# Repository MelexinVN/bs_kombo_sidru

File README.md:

# СИДРУ
## СветоИзлучающее Декоративное Радиоуправляемое Устройство

В рамках проекта ["КомБО"](https://github.com/MelexinVN/bs_kombo) разработано декоративное устройство на адресных светодиодах, управляемое по радиоканалу.

Устройство состоит из двух частей - декоративная часть и пульт управления.

Обе части содержат схему управления на микроконтроллере stm32f030f4p6, радиомодуль nrf24l01+, и схему питания.
В декоративной части микроконтроллер управляет адресными светодиодами ws2812. 
В данном случае светодиоды расположены на модуле в виде кольца (могут быть отдельными модулями, в виде светодиодной ленты и т.п.)

В пульте управления микроконтроллер в зависимости от состояния чувствительного элемента отправляет различные команды в ответ на запросы декоративного устройства.

Здесь в качестве чувствительных элементов используются датчики касания TTP223 (могут быть использованы кнопки, выходы реле, герконы и т.п.)

As part of the "КомБО" project, a decorative device based on addressable LEDs, controlled via a radio channel, has been developed.

The device consists of two parts - a decorative part and a control panel.

Both parts contain a control circuit on the stm32f030f4p6 microcontroller, an nrf24l01+ radio module, and a power supply circuit.
In the decorative part, the microcontroller controls the ws2812 addressable LEDs.
In this case, the LEDs are located on the module in the form of a ring (can be separate modules, in the form of an LED strip, etc.)

In the control panel, the microcontroller, depending on the state of the sensitive element, sends various commands in response to requests from the decorative device.

Here, TTP223 touch sensors are used as sensitive elements (buttons, relays, etc. can be used)

## Схема соединений пульта управления. Control panel connection diagram

## Схема соединений декоративной части. Connection diagram of the decorative part

## Пример готового устройства. Example of a finished device

### Планы по развитию:
- **Добавление новых световых эффектов**
- **Добавление исполнений для других микроконтроллеров и большего числа светодиодов**
- **Проекты исходников на других IDE, в частности STM32CubeIDE**
- **Пример исполнения для подсветки комнаты**

### Development plans:
- **Adding new lighting effects**
- **Add versions for other microcontrollers and more LEDs**
- **Source projects on other IDEs, in particular STM32CubeIDE**
- **Example of design for room lighting**

### Репозиторий содержит:
- ***Исполняемые файлы и исходники ПО декоративной части и пульта управления***. Программы разработаны в Keil µVision V5.38.0.0 (MDK-Lite).
- ***Гербер-файлы и исходники проектов используемых печатных плат***. Платы разработаны в KiCad 7.0.1, дополнительно в папках проекта можно найти архив 3д-моделей компонентов, а также интерактивный список компонентов (BOM).
- ***STL-файлы и исходники 3д-моделей используемых 3д-печатных деталей и корпусов***. Модели разработаны в OpenSCAD version 2021.01.

### The repository contains:
- ***Executable files and software sources for the decorative part and the control panel***. The programs were developed in Keil µVision V5.38.0.0 (MDK-Lite).
- ***Gerber files and source codes for designs of printed circuit boards used***. The boards were developed in KiCad 7.0.1; in addition, in the project folders you can find an archive of 3D models of components, as well as an interactive list of components (BOM).
- ***STL files and sources of 3D models of used 3D printed parts and cases***. The models were developed in OpenSCAD version 2021.01.

## Наши ресурсы:

### Основной репозиторий: [bs_kombo](https://github.com/MelexinVN/bs_kombo)

### Электронная почта: 		    [bskombo@yandex.ru](bskombo@yandex.ru)

### Социальные сети:

- паблик ВКонтакте: 			  [vk.com/bs_kombo](https://vk.com/bs_kombo)
- Telegram-канал: 	        [t.me/bskombo](https://t.me/bskombo)
- Telegram-чат: 	          [t.me/bs_kombo_chat](https://t.me/bs_kombo_chat)

### Авторы всегда рады отзывам и любым конструктивным предложениям по улучшению проекта! 
### The authors are always happy to receive feedback and any constructive suggestions for improving the project!

## Лицензия
Проект распространяется под лицензией Creative Commons Attribution-ShareAlike 4.0 [CC BY-SA 4.0](https://creativecommons.org/licenses/by-sa/4.0/), 
а программное обеспечение - под лицензией GNU General Public License v3.0 [GPL-3.0 license](https://github.com/MelexinVN/bs_kombo/blob/main/LICENSE)

## License
This project is licensed under the Creative Commons 4.0 license with Attribution-ShareAlike [CC BY-SA 4.0](https://creativecommons.org/licenses/by-sa/4.0/), 
and the software is licensed under the GNU General Public License v3.0 [GPL-3.0 license](https://github.com/MelexinVN/bs_kombo/blob/main/LICENSE)

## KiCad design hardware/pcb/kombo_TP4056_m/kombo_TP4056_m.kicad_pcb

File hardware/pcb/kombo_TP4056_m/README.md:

### Плата питания с модулем контроллером заряда TP4056.
### Расположение выходов питания соответствует плате kombo_nrf24_stm32f030, плюсовой контакт разомкнут монтажными отверстиями под переключатель

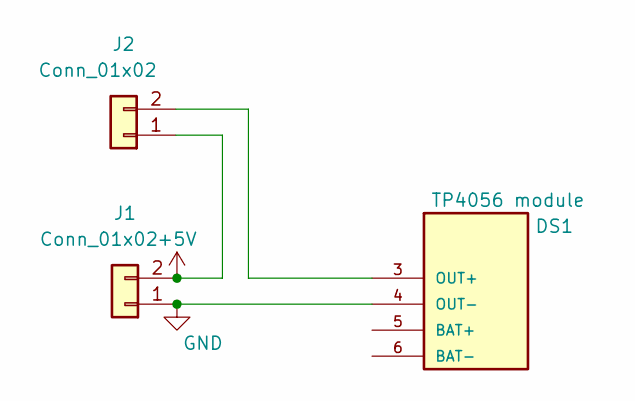
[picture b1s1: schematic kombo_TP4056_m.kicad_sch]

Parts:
DS1: TP4056 module; TP4056-18650; PARTREV N/A
J1, J2: Conn_01x02; PinHeader_1x02_P2.54mm_Vertical

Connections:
+5V: J1.2, J2.1
GND: DS1.4 (OUT-), J1.1
unnamed: DS1.3 (OUT+), J2.2

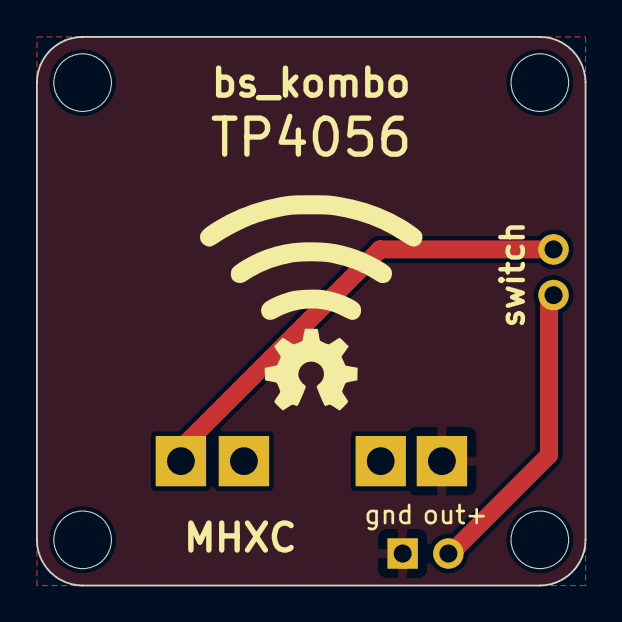
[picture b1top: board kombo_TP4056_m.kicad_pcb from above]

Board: 2 copper layers, 30.5 x 30.5 mm, 3 parts (1 on the bottom side), 3 nets.

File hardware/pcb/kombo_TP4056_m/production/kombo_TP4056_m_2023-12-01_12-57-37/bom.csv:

Designator,Footprint,Quantity,Value,LCSC Part #
DS1,TP4056-18650,1,TP4056 module,
"J1, J2",PinHeader_1x02_P2.54mm_Vertical,2,Conn_01x02,

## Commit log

2023-12-18 correction
2023-12-19 add photo
